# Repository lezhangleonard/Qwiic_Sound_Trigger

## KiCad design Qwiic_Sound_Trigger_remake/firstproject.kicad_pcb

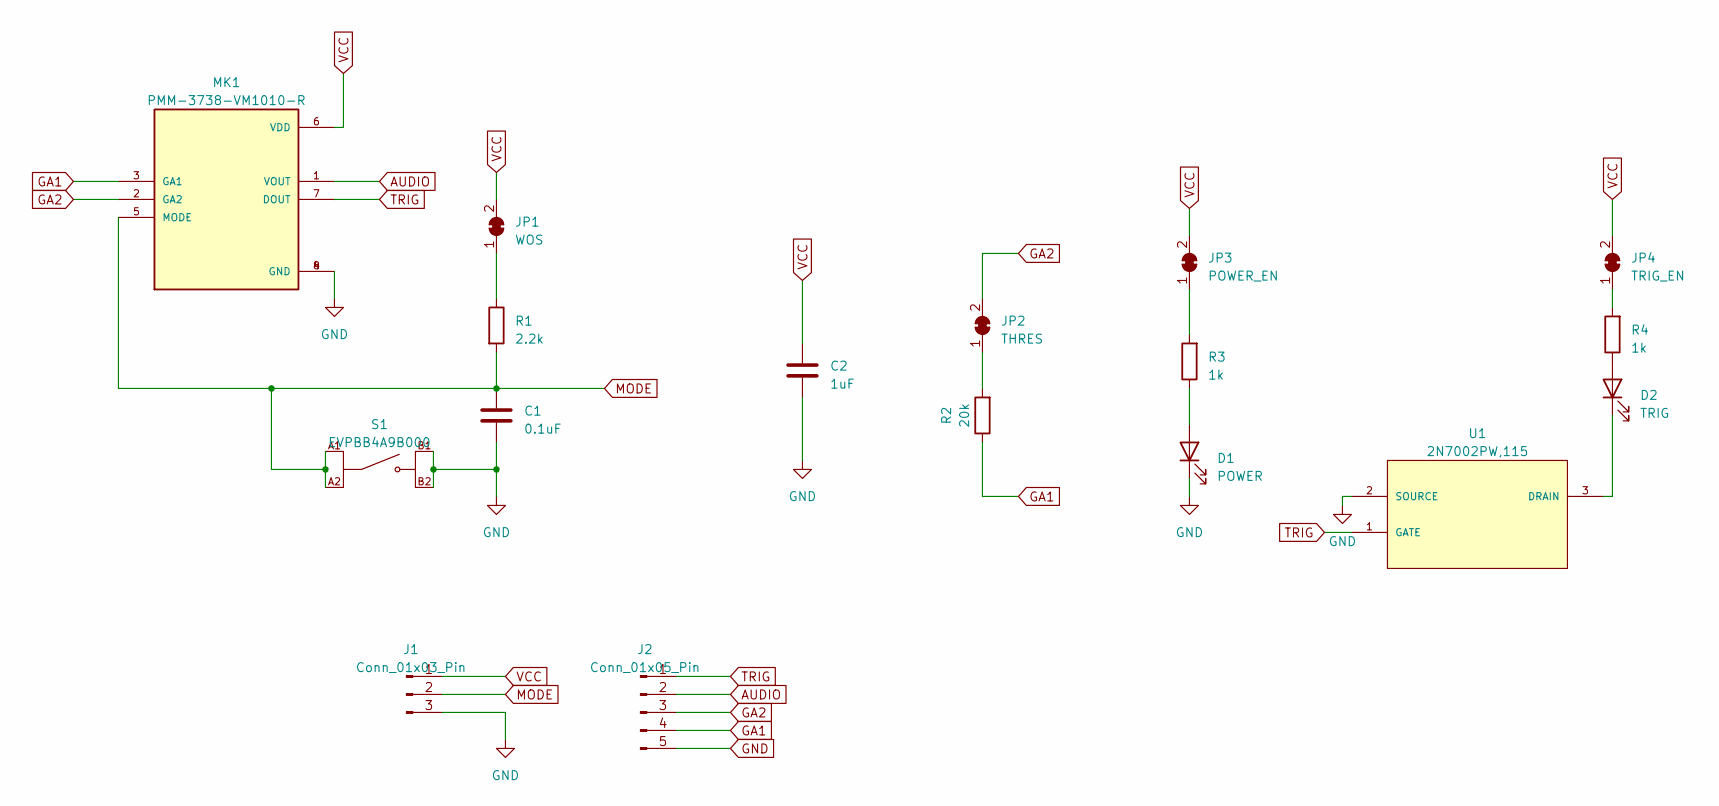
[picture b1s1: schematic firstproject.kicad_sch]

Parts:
C1: 0.1uF; C_0402_1005Metric; MPN CL05A104KA5NNNC; DIGIKEY_PART 1276-1043-2-ND
C2: 1uF; C_0402_1005Metric; MPN CL05A105KP5NNNC; DIGIKEY_PART 1276-1076-2-ND
D1: POWER; LED_0603_1608Metric; MPN LTST-C191KRKT; DIGIKEY_PART 160-1447-2-ND
D2: TRIG; LED_0603_1608Metric; MPN LTST-C191KGKT; DIGIKEY_PART 160-1446-2-ND
J1: Conn_01x03_Pin; PinHeader_1x03_P2.54mm_Vertical
J2: Conn_01x05_Pin; PinHeader_1x05_P2.54mm_Vertical
JP1: WOS; SolderJumper-2_P1.3mm_Bridged2Bar_Pad1.0x1.5mm
JP2: THRES; SolderJumper-2_P1.3mm_Bridged2Bar_Pad1.0x1.5mm
JP3: POWER_EN; SolderJumper-2_P1.3mm_Bridged2Bar_Pad1.0x1.5mm
JP4: TRIG_EN; SolderJumper-2_P1.3mm_Bridged2Bar_Pad1.0x1.5mm
MK1: PMM-3738-VM1010-R; MIC_PMM-3738-VM1010-R; MPN PMM-3738-VM1010-R; DIGIKEY_PART 668-1585-2-ND
R1: 2.2k; R_0402_1005Metric; MPN AC0402JR-072K2L; DIGIKEY_PART YAG3536TR-ND
R2: 20k; R_0402_1005Metric; MPN RT0402BRD0720KL; DIGIKEY_PART YAG1388TR-ND
R3, R4: 1k; R_0402_1005Metric; MPN RT0402BRE071KL; DIGIKEY_PART YAG2306TR-ND
S1: EVPBB4A9B000; SW_EVPBB4A9B000; MPN EVPBB4A9B000; DIGIKEY_PART P19888CT-ND
U1: 2N7002PW,115; SOT65P210X110-3N; MPN 2N7002PW,115; DIGIKEY_PART 1727-4793-2-ND

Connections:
AUDIO: J2.2, MK1.1 (VOUT)
GA1: J2.4, MK1.3 (GA1), R2.1
GA2: J2.3, JP2.2 (B), MK1.2 (GA2)
GND: C1.2, C2.2, D1.1 (K), J1.3, J2.5, MK1.4 (GND), MK1.8 (GND), S1.B1, S1.B2, U1.2 (SOURCE)
MODE: C1.1, J1.2, MK1.5 (MODE), R1.2, S1.A1, S1.A2
unnamed: D1.2 (A), R3.1
unnamed: D2.2 (A), R4.1
unnamed: D2.1 (K), U1.3 (DRAIN)
unnamed: JP1.1 (A), R1.1
unnamed: JP2.1 (A), R2.2
unnamed: JP3.1 (A), R3.2
unnamed: JP4.1 (A), R4.2
TRIG: J2.1, MK1.7 (DOUT), U1.1 (GATE)
VCC: C2.1, J1.1, JP1.2 (B), JP3.2 (B), JP4.2 (B), MK1.6 (VDD)

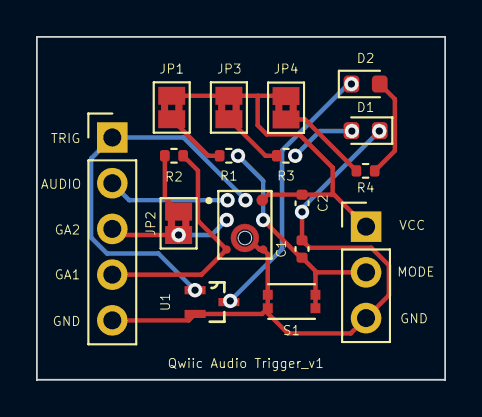
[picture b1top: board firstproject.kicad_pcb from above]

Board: 2 copper layers, 22.7 x 19.0 mm, 17 parts (0 on the bottom side), 14 nets.

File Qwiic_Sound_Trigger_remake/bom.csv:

"Reference","Value","Footprint","Datasheet","DIGIKEY_PART","MANUFACTURER","MPN","Qty"
"C1","0.1uF","Capacitor_SMD:C_0402_1005Metric","~","1276-1043-2-ND","Samsung Electro-Mechanics","CL05A104KA5NNNC","1"
"C2","1uF","Capacitor_SMD:C_0402_1005Metric","~","1276-1076-2-ND","Samsung Electro-Mechanics","CL05A105KP5NNNC","1"
"D1","POWER","LED_SMD:LED_0603_1608Metric","~","160-1447-2-ND","Lite-on Inc","LTST-C191KRKT","1"
"D2","TRIG","LED_SMD:LED_0603_1608Metric","~","160-1446-2-ND","Lite-on Inc","LTST-C191KGKT","1"
"J1","Conn_01x03_Pin","Connector_PinHeader_2.54mm:PinHeader_1x03_P2.54mm_Vertical","~","","","","1"
"J2","Conn_01x05_Pin","Connector_PinHeader_2.54mm:PinHeader_1x05_P2.54mm_Vertical","~","","","","1"
"JP1","WOS","Jumper:SolderJumper-2_P1.3mm_Bridged2Bar_Pad1.0x1.5mm","~","","","","1"
"JP2","THRES","Jumper:SolderJumper-2_P1.3mm_Bridged2Bar_Pad1.0x1.5mm","~","","","","1"
"JP3","POWER_EN","Jumper:SolderJumper-2_P1.3mm_Bridged2Bar_Pad1.0x1.5mm","~","","","","1"
"JP4","TRIG_EN","Jumper:SolderJumper-2_P1.3mm_Bridged2Bar_Pad1.0x1.5mm","~","","","","1"
"MK1","PMM-3738-VM1010-R","PMM-3738-VM1010-R:MIC_PMM-3738-VM1010-R","","668-1585-2-ND","PUI Audio","PMM-3738-VM1010-R","1"
"R1","2.2k","Resistor_SMD:R_0402_1005Metric","~","YAG3536TR-ND","YAGEO","AC0402JR-072K2L","1"
"R2","20k","Resistor_SMD:R_0402_1005Metric","~","YAG1388TR-ND","YAGEO","RT0402BRD0720KL","1"
"R3, R4","1k","Resistor_SMD:R_0402_1005Metric","~","YAG2306TR-ND","YAGEO","RT0402BRE071KL","2"
"S1","EVPBB4A9B000","SW_EVPBB4A9B000","","P19888CT-ND","Panasonic Electronic","EVPBB4A9B000","1"
"U1","2N7002PW,115","2N7002PW_115:SOT65P210X110-3N","","1727-4793-2-ND","Nexperia USA Inc.","2N7002PW,115","1"

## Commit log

2023-04-30 remake
